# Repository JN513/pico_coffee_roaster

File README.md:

# Pico Coffee Roaster

Mini torrador de café baseado no Raspberry Pi Pico.

Este firmware é capaz de realizar o controle de uma resistência utilizando um triac, além do controle de um motor e de um fan via PWM.
Também estão disponíveis periféricos como displays, termistores NTC, termopares PT0, controle PID, entre outros.

O projeto utiliza o pico-sdk como base.
Além do pico-sdk instalado e configurado no PATH do ambiente, também é necessário instalar o pico-extras.

## Build e load

Para compilar o projeto utilize:

```bash
mkdir -p build
cd build
cmake ..
make -j$(nproc)
```

Para enviar o firmware para o Pico utilize:

```bash
cd build
picotool load pico_roster.uf2 -f
```

Certifique-se de que o `picotool` esteja instalado e disponível no PATH do sistema.

## Dúvidas e Sugestões

Se tiver alguma dúvida ou sugestão, sinta-se à vontade para utilizar a seção de [ISSUES](https://github.com/JN513/pico_coffee_roaster/issues) no GitHub. Contribuições são bem-vindas e todos os [Pull requests](https://github.com/JN513/pico_coffee_roaster/pulls) serão revisados e, se possível, mesclados.

## Contribuição

Se deseja contribuir com o projeto, sinta-se à vontade para fazê-lo. O arquivo [CONTRIBUTING.md](https://github.com/JN513/pico_coffee_roaster/blob/main/CONTRIBUTING.md) contém as instruções necessárias.

## Licença

Este projeto é licenciado sob a licença [MIT]([https://github.com/JN513/pico_coffee_roaster/blob/main/LICENSE](https://github.com/JN513/pico_coffee_roaster/blob/main/LICENSE)), que concede total liberdade para uso.

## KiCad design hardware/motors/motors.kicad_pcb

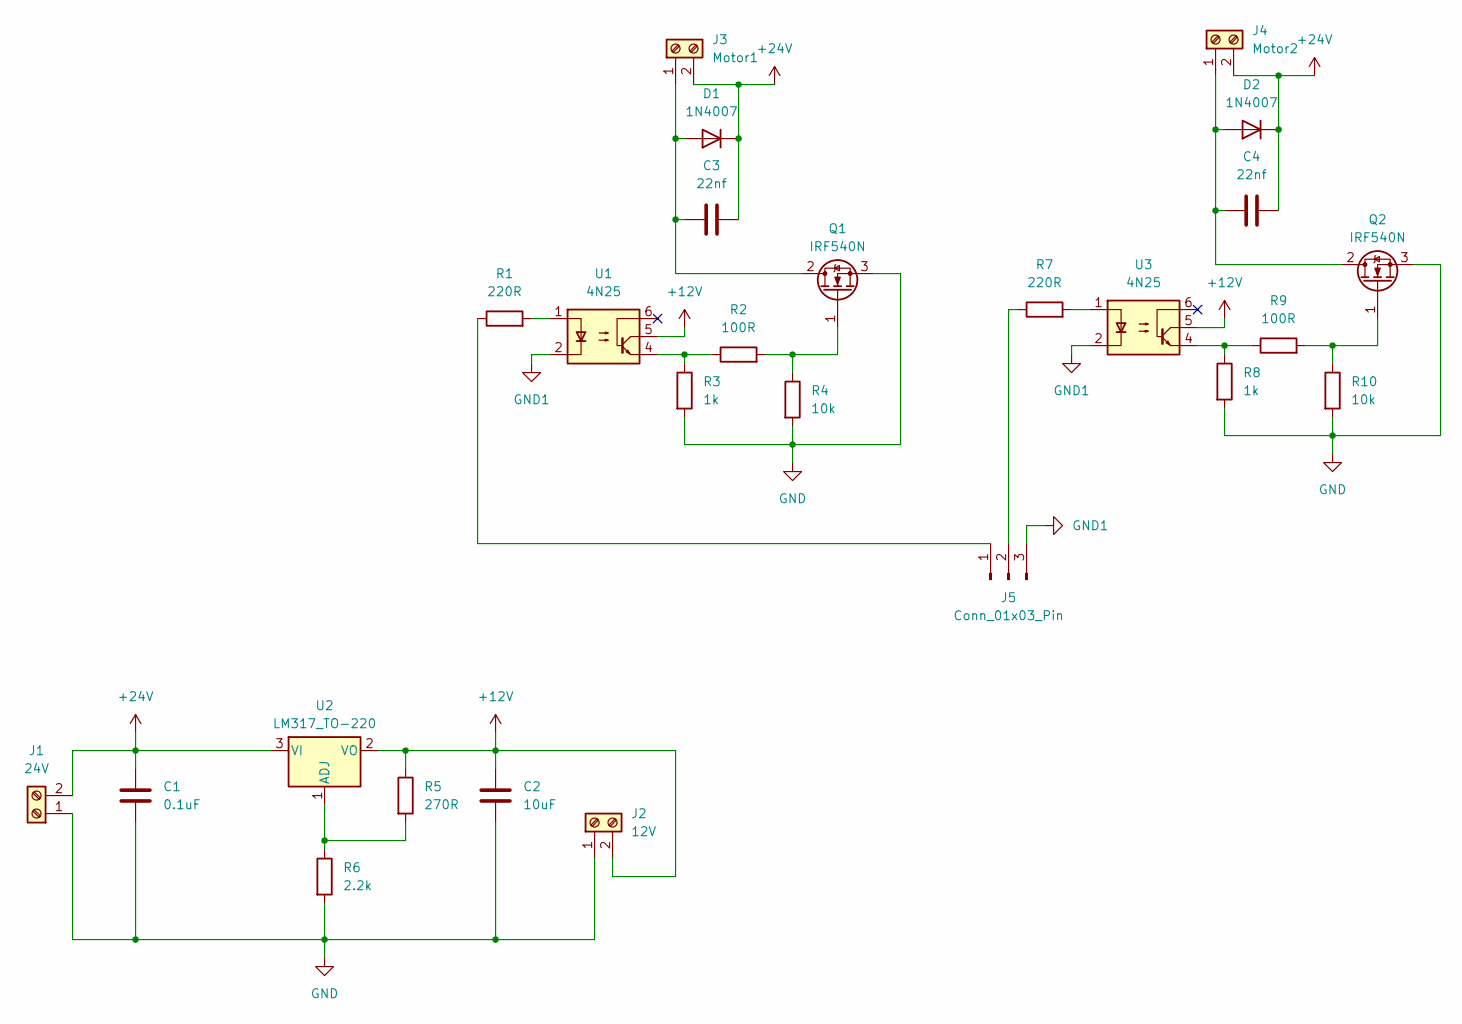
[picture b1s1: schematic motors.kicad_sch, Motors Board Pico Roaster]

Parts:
C1: 0.1uF; CP_Radial_D4.0mm_P2.00mm
C2: 10uF; CP_Radial_D4.0mm_P2.00mm
C3, C4: 22nf; C_Disc_D4.7mm_W2.5mm_P5.00mm
D1, D2: 1N4007; D_DO-41_SOD81_P10.16mm_Horizontal
J1: 24V; Altech_AK100_1x02_P5.00mm
J2: 12V; Altech_AK100_1x02_P5.00mm
J3: Motor1; Altech_AK100_1x02_P5.00mm
J4: Motor2; Altech_AK100_1x02_P5.00mm
J5: Conn_01x03_Pin; PinHeader_1x03_P2.54mm_Vertical
Q1, Q2: IRF540N; TO-220-3_Vertical
R1, R7: 220R; R_Axial_DIN0204_L3.6mm_D1.6mm_P7.62mm_Horizontal
R2, R9: 100R; R_Axial_DIN0204_L3.6mm_D1.6mm_P7.62mm_Horizontal
R3, R8: 1k; R_Axial_DIN0204_L3.6mm_D1.6mm_P7.62mm_Horizontal
R4, R10: 10k; R_Axial_DIN0204_L3.6mm_D1.6mm_P7.62mm_Horizontal
R5: 270R; R_Axial_DIN0204_L3.6mm_D1.6mm_P7.62mm_Horizontal
R6: 2.2k; R_Axial_DIN0204_L3.6mm_D1.6mm_P7.62mm_Horizontal
U1, U3: 4N25; DIP-6_W7.62mm
U2: LM317_TO-220; TO-220-3_Vertical

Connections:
+12V: C2.1, J2.2, R5.1, U1.5, U2.2 (VO), U3.5
+24V: C1.1, C3.2, C4.2, D1.1 (K), D2.1 (K), J1.2, J3.2, J4.2, U2.3 (VI)
GND: C1.2, C2.2, J1.1, J2.1, Q1.3 (S), Q2.3 (S), R3.2, R4.2, R6.2, R8.2, R10.2
GND1: J5.3, U1.2, U3.2
unnamed: C3.1, D1.2 (A), J3.1, Q1.2 (D)
unnamed: C4.1, D2.2 (A), J4.1, Q2.2 (D)
unnamed: J5.1, R1.1
unnamed: J5.2, R7.1
unnamed: Q1.1 (G), R2.2, R4.1
unnamed: Q2.1 (G), R9.2, R10.1
unnamed: R1.2, U1.1
unnamed: R2.1, R3.1, U1.4
unnamed: R7.2, U3.1
unnamed: R8.1, R9.1, U3.4
unnamed: R5.2, R6.1, U2.1 (ADJ)

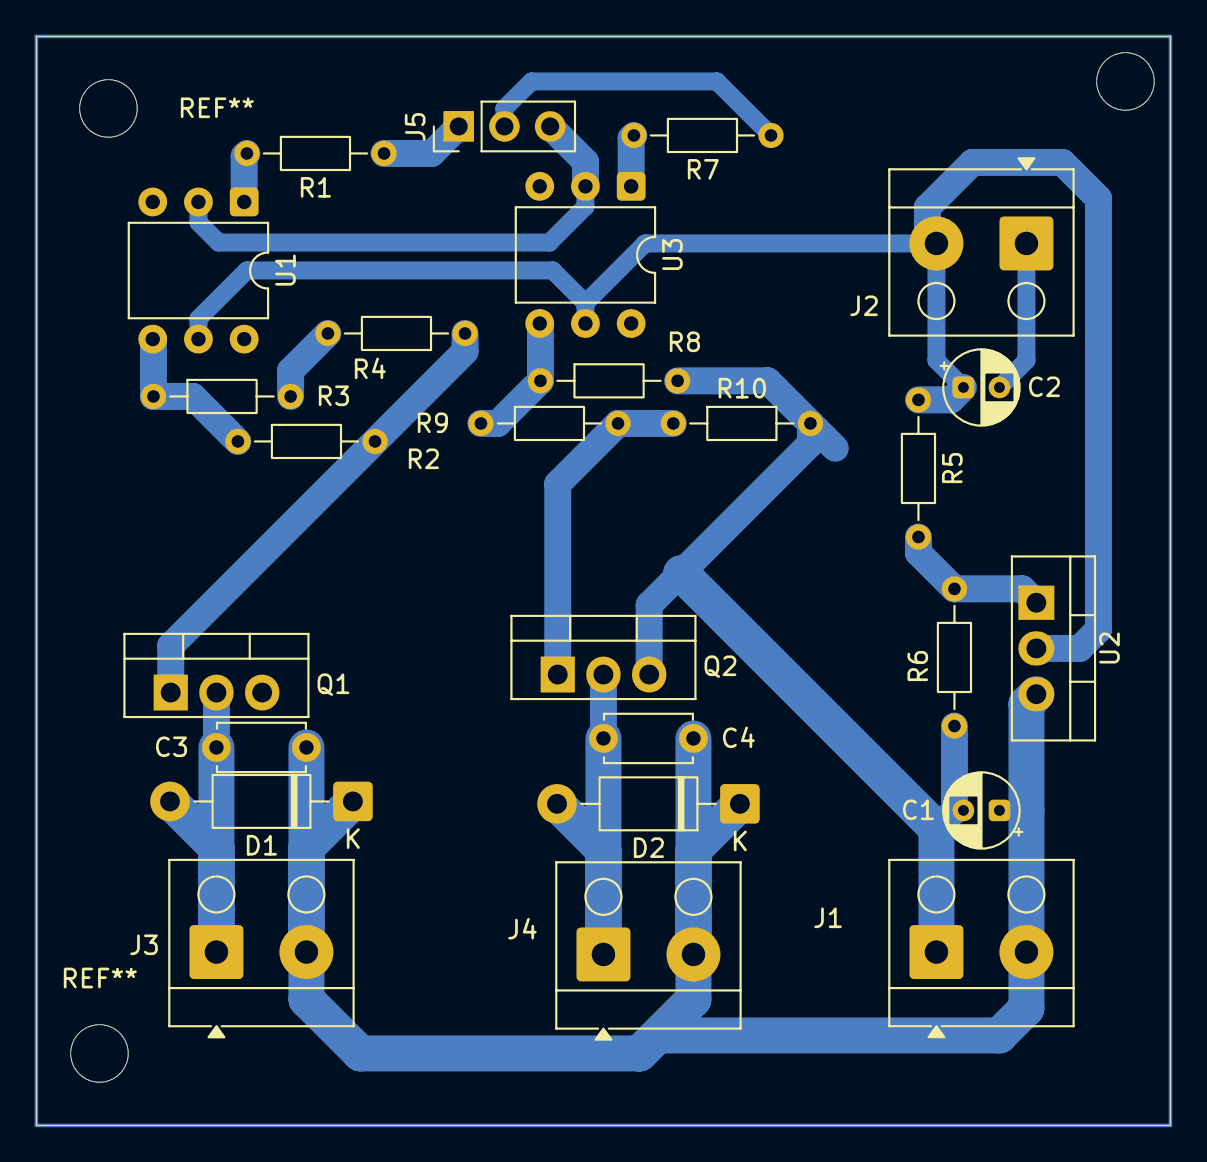
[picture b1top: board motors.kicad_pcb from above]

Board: 2 copper layers, 63.0 x 60.5 mm, 26 parts (0 on the bottom side), 15 nets.

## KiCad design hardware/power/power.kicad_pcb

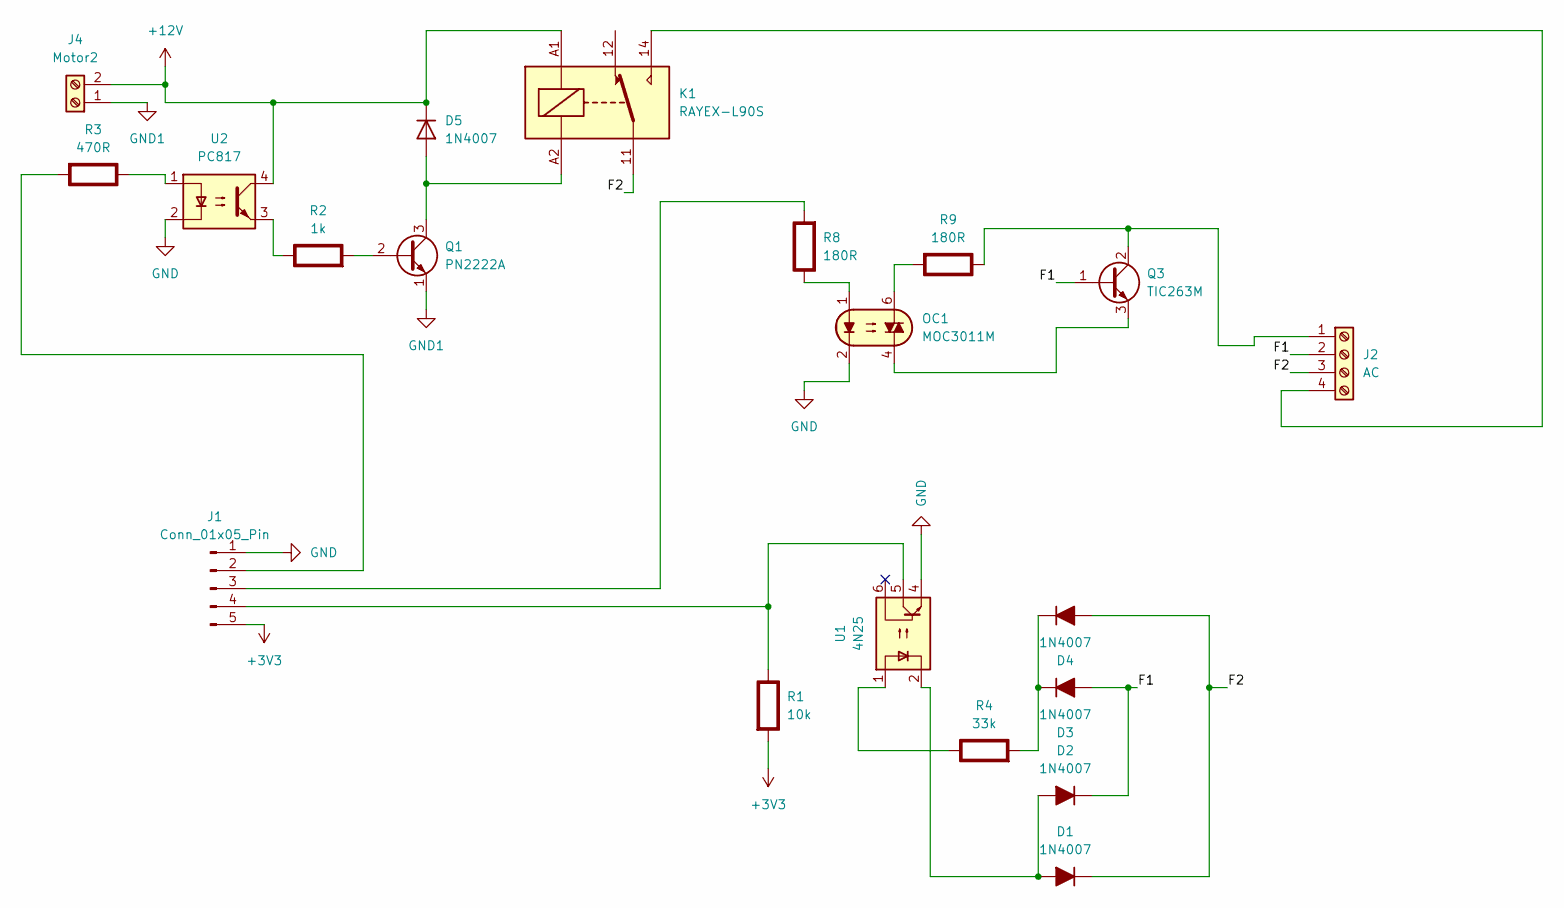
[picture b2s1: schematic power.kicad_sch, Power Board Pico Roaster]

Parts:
D1, D2, D3, D4, D5: 1N4007; D_DO-41_SOD81_P10.16mm_Horizontal
J1: Conn_01x05_Pin; PinHeader_1x05_P2.54mm_Vertical
J2: AC; Altech_AK100_1x04_P5.00mm
J4: Motor2; Altech_AK100_1x02_P5.00mm
K1: RAYEX-L90S; Relay_SPDT_RAYEX-L90S
OC1: MOC3011M; DIP-6_W7.62mm_LongPads
Q1: PN2222A; TO-92_Inline
Q3: TIC263M; TO-218-3_Vertical
R1: 10k; R_Axial_DIN0207_L6.3mm_D2.5mm_P10.16mm_Horizontal; Rating W
R2: 1k; R_Axial_DIN0207_L6.3mm_D2.5mm_P10.16mm_Horizontal; Rating W
R3: 470R; R_Axial_DIN0207_L6.3mm_D2.5mm_P10.16mm_Horizontal; Rating W
R4: 33k; R_Axial_DIN0207_L6.3mm_D2.5mm_P10.16mm_Horizontal; Rating W
R8: 180R; R_Axial_DIN0207_L6.3mm_D2.5mm_P10.16mm_Horizontal; Rating W
R9: 180R; R_Axial_DIN0414_L11.9mm_D4.5mm_P20.32mm_Horizontal; Rating W
U1: 4N25; DIP-6_W7.62mm
U2: PC817; DIP-4_W7.62mm

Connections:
+3V3: J1.5, R1.2 (-)
+12V: D5.1 (K), J4.2, K1.A1, U2.4
/F1: D2.1 (K), D3.2 (A), J2.2, Q3.1 (B)
/F2: D1.1 (K), D4.2 (A), J2.3, K1.11
GND: J1.1, OC1.2, U1.4, U2.2
GND1: J4.1, Q1.1 (E)
unnamed: D1.2 (A), D2.2 (A), U1.2
unnamed: D3.1 (K), D4.1 (K), R4.2 (-)
unnamed: D5.2 (A), K1.A2, Q1.3 (C)
unnamed: J1.2, R3.2 (-)
unnamed: J1.3, R8.2 (-)
unnamed: J1.4, R1.1 (+), U1.5
unnamed: J2.1, Q3.2 (C), R9.1 (+)
unnamed: J2.4, K1.14
unnamed: Q1.2 (B), R2.2 (-)
unnamed: OC1.4, Q3.3 (E)
unnamed: R2.1 (+), U2.3
unnamed: R3.1 (+), U2.1
unnamed: R4.1 (+), U1.1
unnamed: OC1.1, R8.1 (+)
unnamed: OC1.6, R9.2 (-)

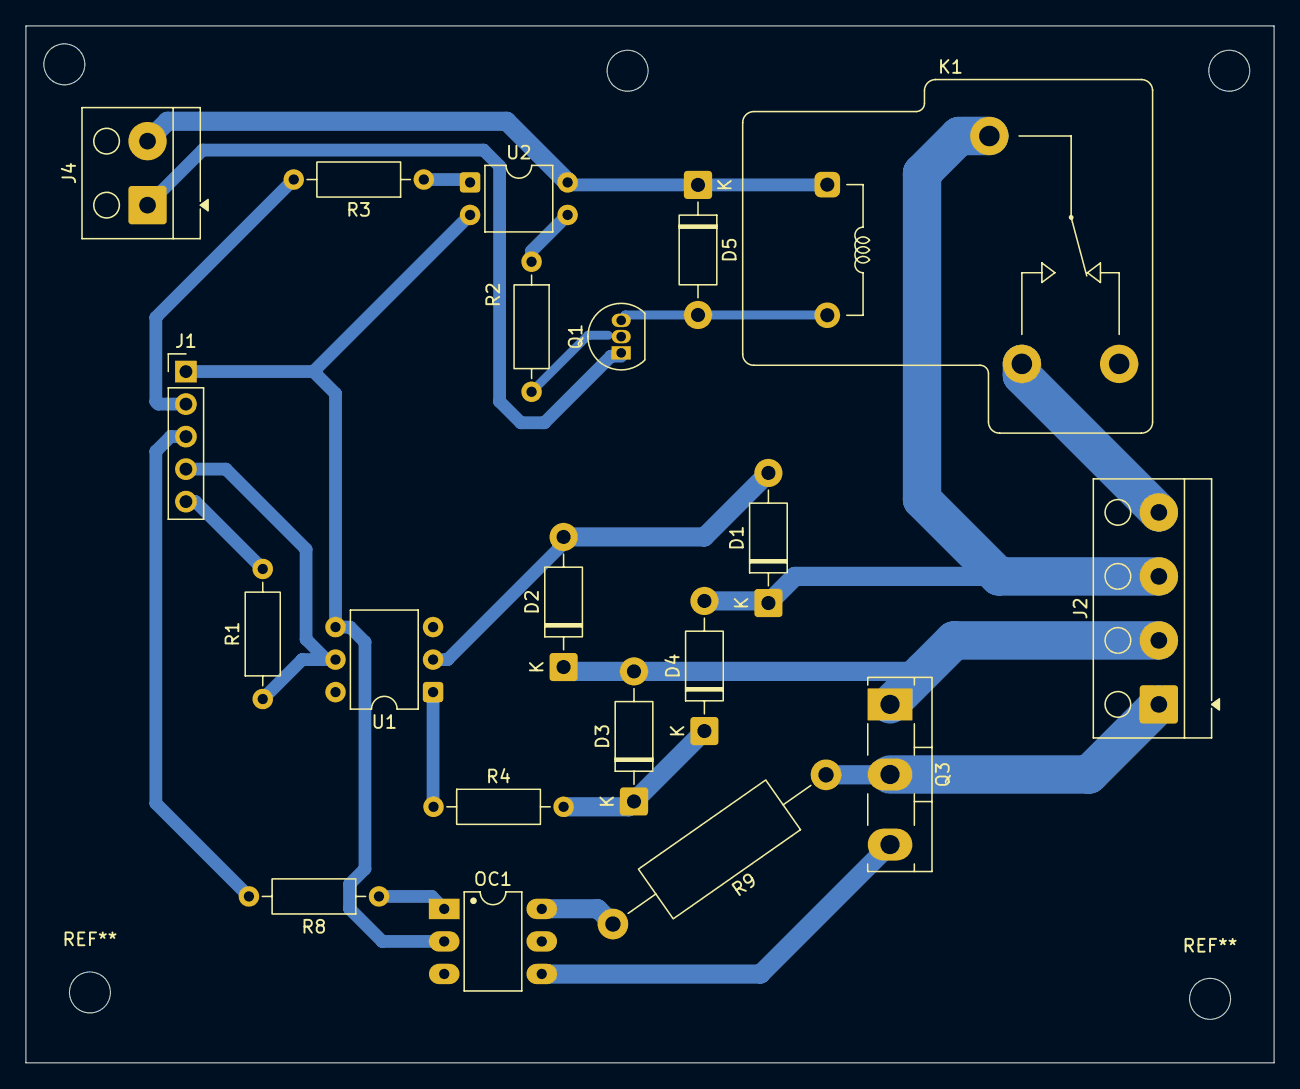
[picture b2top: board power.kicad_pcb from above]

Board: 2 copper layers, 97.5 x 81.0 mm, 20 parts (0 on the bottom side), 21 nets.

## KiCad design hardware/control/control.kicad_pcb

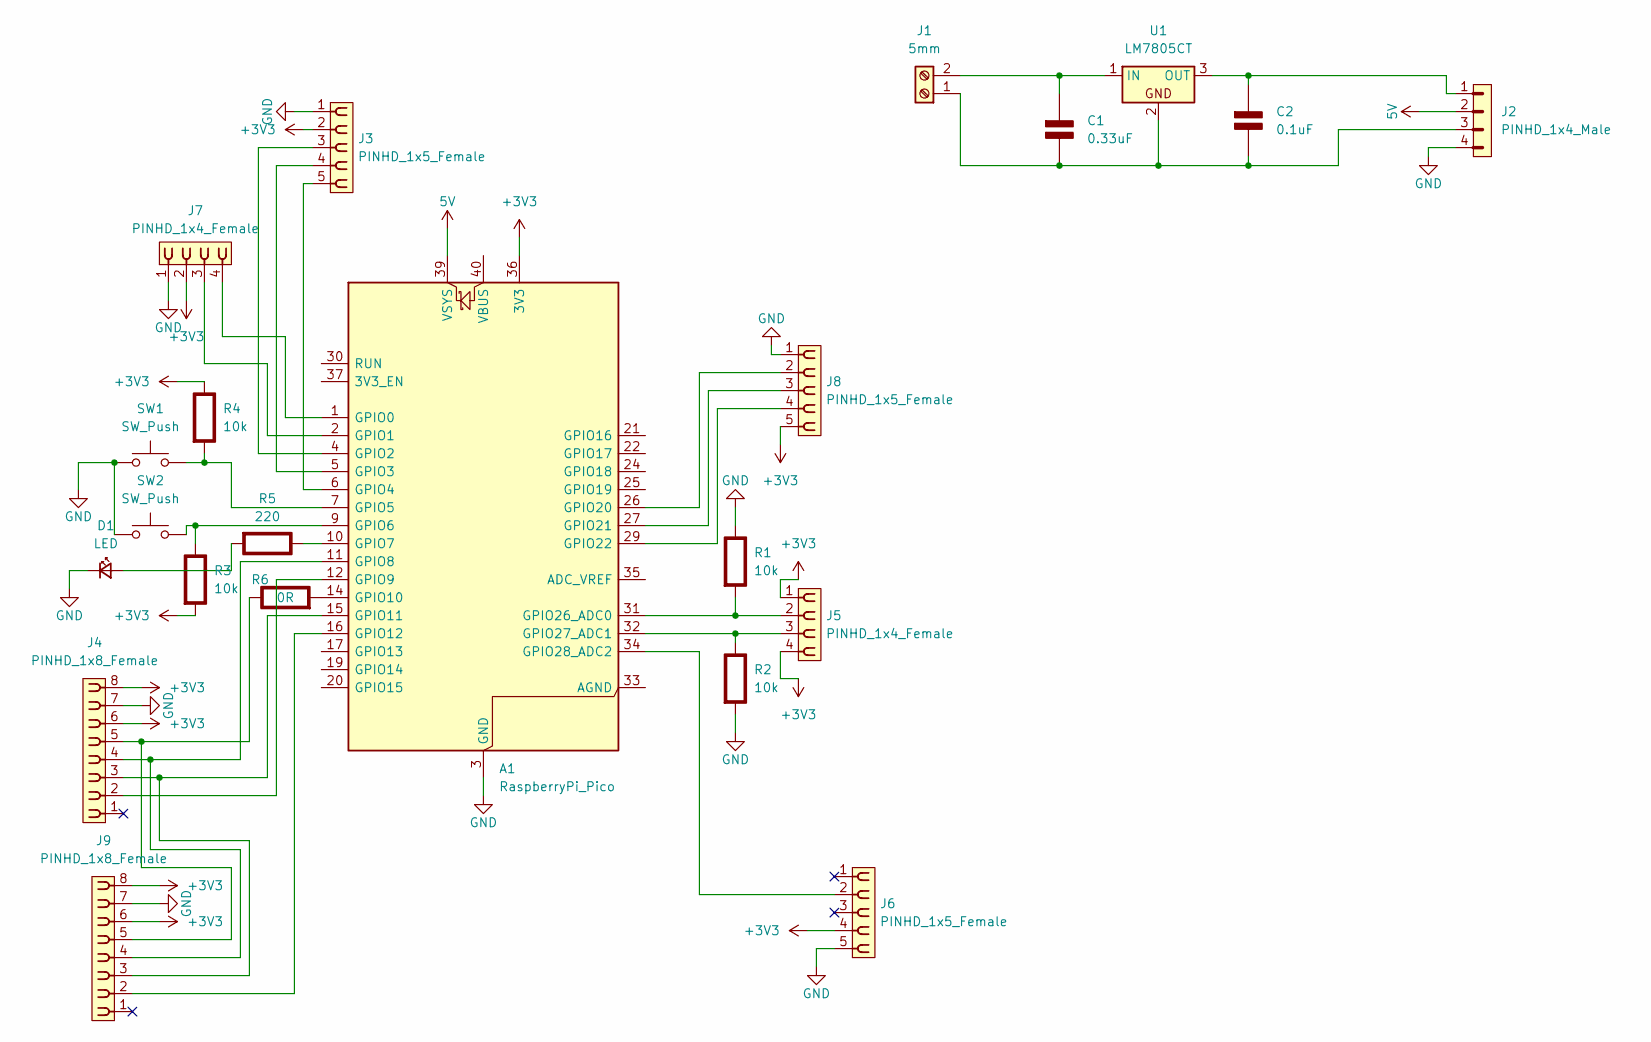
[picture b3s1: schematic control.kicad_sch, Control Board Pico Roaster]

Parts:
A1: RaspberryPi_Pico; RaspberryPi_Pico_Common_Unspecified
C1: 0.33uF; C_Radial_D5.0mm_H7.0mm_P2.00mm; Rating V
C2: 0.1uF; C_Radial_D5.0mm_H7.0mm_P2.00mm; Rating V
D1: LED; LED_D5.0mm
J1: 5mm; ScrewTerminal_1x02_P5.0mm
J2: PINHD_1x4_Male; PinHeader_1x04_P2.54mm_Vertical
J3, J6, J8: PINHD_1x5_Female; PinSocket_1x05_P2.54mm_Vertical
J4, J9: PINHD_1x8_Female; PinSocket_1x08_P2.54mm_Vertical
J5, J7: PINHD_1x4_Female; PinSocket_1x04_P2.54mm_Vertical
R1, R2, R3, R4: 10k; R_Axial_DIN0207_L6.3mm_D2.5mm_P10.16mm_Horizontal; Rating W
R5: 220; R_Axial_DIN0207_L6.3mm_D2.5mm_P10.16mm_Horizontal; Rating W
R6: 0R; R_Axial_DIN0207_L6.3mm_D2.5mm_P10.16mm_Horizontal; Rating W
SW1, SW2: SW_Push; SW_PUSH_1P1T_6x3.5mm_H4.3_APEM_MJTP1243
U1: LM7805CT; TO-220-3_Vertical

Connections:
5V: A1.39 (VSYS), J2.2
+3V3: A1.36 (3V3), J3.2, J4.6, J4.8, J5.1, J5.4, J6.4, J7.2, J8.5, J9.6, J9.8, R3.2 (-), R4.1 (+)
GND: A1.3 (GND), A1.8 (GND), A1.13 (GND), A1.18 (GND), A1.23 (GND), A1.28 (GND), A1.38 (GND), D1.1 (K), J2.4, J3.1, J4.7, J6.5, J7.1, J8.1, J9.7, R1.1 (+), R2.2 (-), SW1.1, SW2.1
unnamed: A1.1 (GPIO0), J7.4
unnamed: A1.2 (GPIO1), J7.3
unnamed: A1.4 (GPIO2), J3.3
unnamed: A1.5 (GPIO3), J3.4
unnamed: A1.6 (GPIO4), J3.5
unnamed: A1.7 (GPIO5), R4.2 (-), SW1.2
unnamed: A1.9 (GPIO6), R3.1 (+), SW2.2
unnamed: A1.10 (GPIO7), R5.1 (+)
unnamed: A1.11 (GPIO8), J4.4, J9.4
unnamed: A1.12 (GPIO9), J4.2
unnamed: A1.14 (GPIO10), R6.2 (-)
unnamed: A1.15 (GPIO11), J4.3, J9.3
unnamed: A1.16 (GPIO12), J9.2
unnamed: A1.26 (GPIO20), J8.2
unnamed: A1.27 (GPIO21), J8.3
unnamed: A1.29 (GPIO22), J8.4
unnamed: A1.31 (GPIO26_ADC0), J5.2, R1.2 (-)
unnamed: A1.32 (GPIO27_ADC1), J5.3, R2.1 (+)
unnamed: A1.34 (GPIO28_ADC2), J6.2
unnamed: C1.1 (+), J1.2, U1.1 (IN)
unnamed: C1.2 (-), C2.2 (-), J1.1, J2.3, U1.2
unnamed: C2.1 (+), J2.1, U1.3 (OUT)
unnamed: D1.2 (A), R5.2 (-)
unnamed: J4.5, J9.5, R6.1 (+)

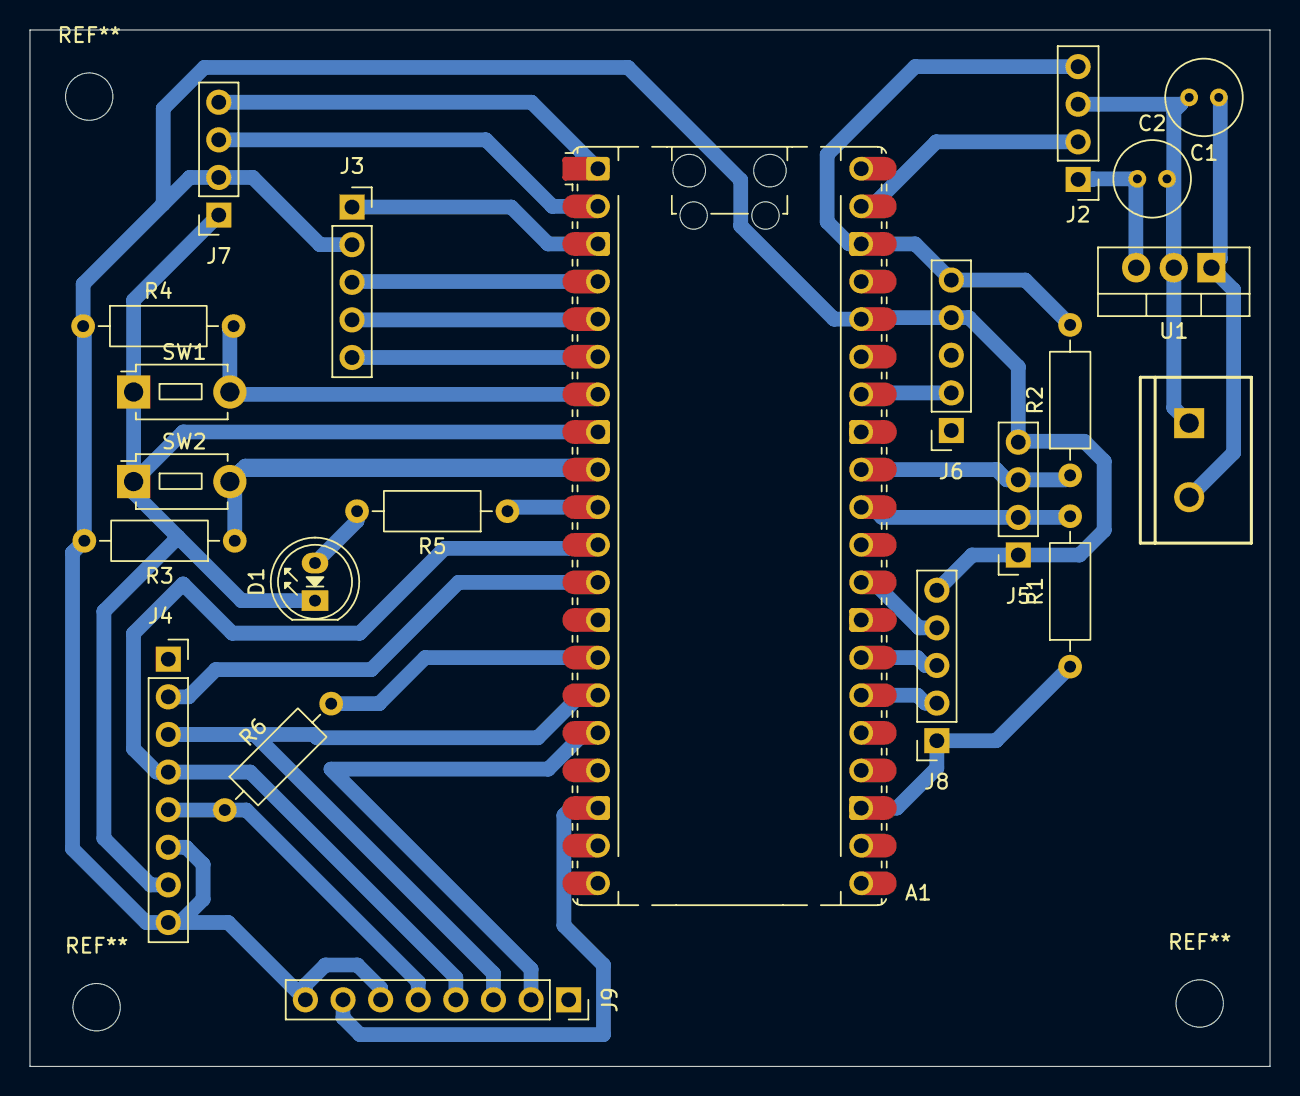
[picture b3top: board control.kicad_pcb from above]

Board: 2 copper layers, 83.8 x 70.0 mm, 22 parts (0 on the bottom side), 27 nets.

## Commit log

2026-02-02 Iniciando projeto
2026-02-03 Implementando funcoes para controle
    Implementando funcoes para controle de potencia do motor via PWM, de
    resistencia via triac e leitura dos thermistores
2026-02-03 Usando timer temporariamente
2026-02-25 Iniciando controle
2026-03-02 Implementando suporte para o Max31865
2026-03-04 Atualizando pinos
2026-03-14 Implementando controle basico
2026-03-15 Implementando controle, display e botoes
2026-03-15 Adicionando sistemas de profiles
2026-03-15 Adicionando novos profiles
2026-03-16 Atualizando auto poweroff
2026-03-17 Integrando RTOS e sistema multicore
2026-03-17 Implementando sistema de Menu
2026-03-17 Escrevendo README e adicionando contributing
2026-03-17 Concertando defines
2026-03-17 Implementando logica inicial de detector de first crack
2026-03-17 Corrigindo comportamento do encoder
2026-03-18 Corrigindo parametros de controle
2026-03-18 Removendo logica separada para encoder
2026-03-18 Adicionando novo profile
2026-03-18 Deployed f925edf with MkDocs version: 1.6.1
2026-03-18 Adicionando Documentação ao projeto
2026-03-18 Adicionando curva do PID os dados enviados ao Artisan
2026-03-19 Criando perfis com suporte a airflow ajustavel
2026-03-19 Adicionando esquematicos ao projeto
2026-03-19 Adicionando case do torrador
2026-03-19 Removendo arquivos indesejados
2026-04-09 Atualizando rotinas
2026-04-09 Adicionando perfil de amendoim
